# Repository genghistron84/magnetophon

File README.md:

# magnetophon
Small footprint version of Tom Whitwell's Magnetophon module

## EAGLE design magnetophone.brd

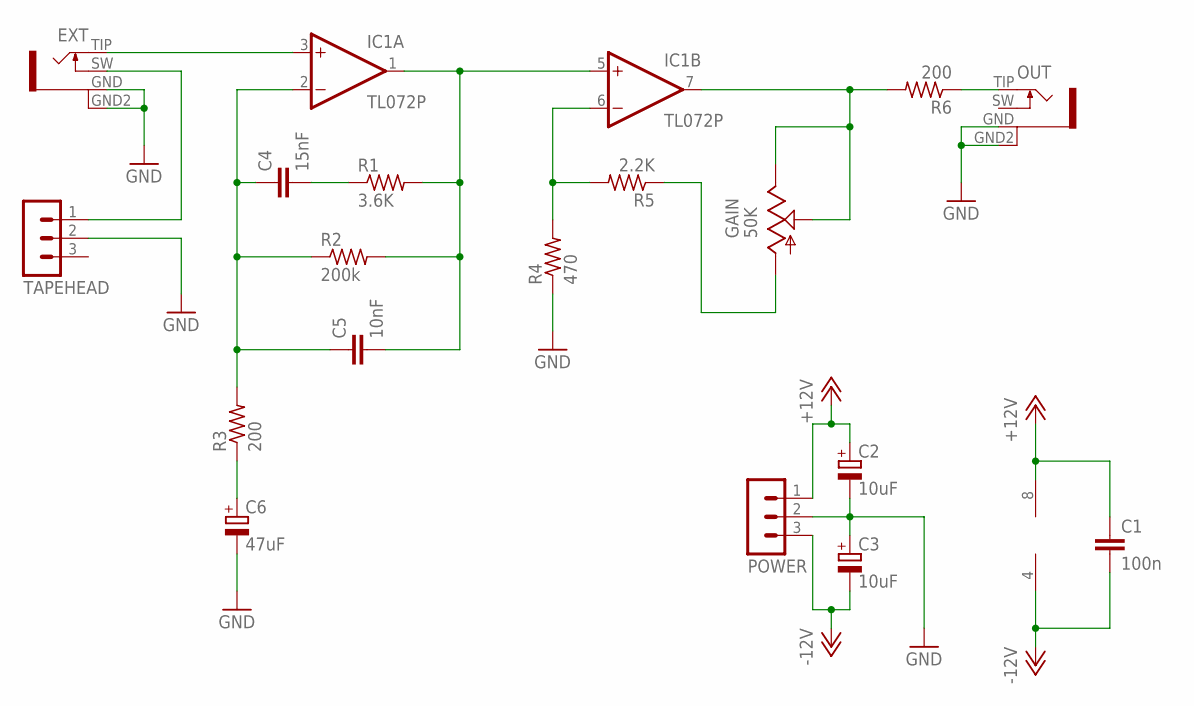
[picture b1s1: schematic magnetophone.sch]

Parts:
C1: 100n; C025-025X050
C2, C3: 10uF; E2,5-6E
C4: 15nF; C025-025X050
C5: 10nF; C025-025X050
C6: 47uF; E2,5-6E
EXT: PJ301BM; PJ301
GAIN: 50K; 9MM_SNAP-IN_POT
IC1: TL072P; DIL08
OUT: PJ301BM; PJ301
POWER: MA03-1
R1: 3.6K; 0207/10
R2: 200k; 0207/10
R3, R6: 200; 0207/10
R4: 470; 0207/10
R5: 2.2K; 0207/10
TAPEHEAD: MA03-1

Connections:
+12V: C1.1, C2.+, IC1.8 (V+), POWER.1
-12V: C1.2, C3.-, IC1.4 (V-), POWER.3
GND: C2.-, C3.+, C6.-, EXT.GND (1), EXT.GND2 (4), OUT.GND (1), OUT.GND2 (4), POWER.2, R4.1, TAPEHEAD.2
unnamed: EXT.SW (3), TAPEHEAD.1
unnamed: C4.1, C5.1, IC1.2 (-IN), R2.1, R3.2
unnamed: C5.2, IC1.1 (OUT), IC1.5 (+IN), R1.2, R2.2
unnamed: C6.+, R3.1
unnamed: EXT.TIP (2), IC1.3 (+IN)
unnamed: C4.2, R1.1
unnamed: IC1.6 (-IN), R4.2, R5.2
unnamed: GAIN.1 (A), R5.1
unnamed: GAIN.2 (S), GAIN.3 (E), IC1.7 (OUT), R6.2
unnamed: OUT.TIP (2), R6.1

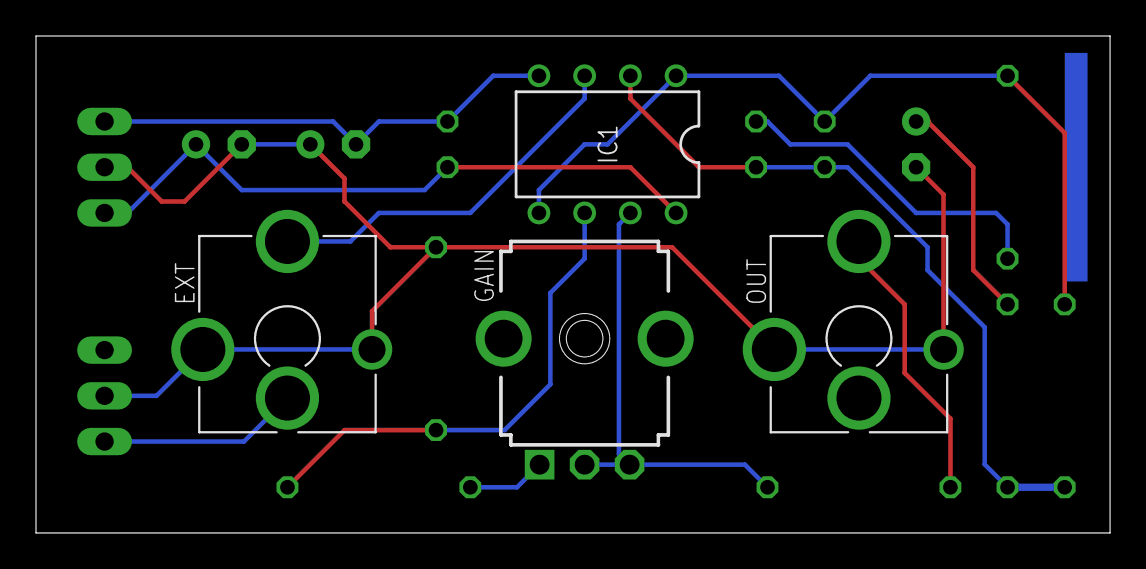
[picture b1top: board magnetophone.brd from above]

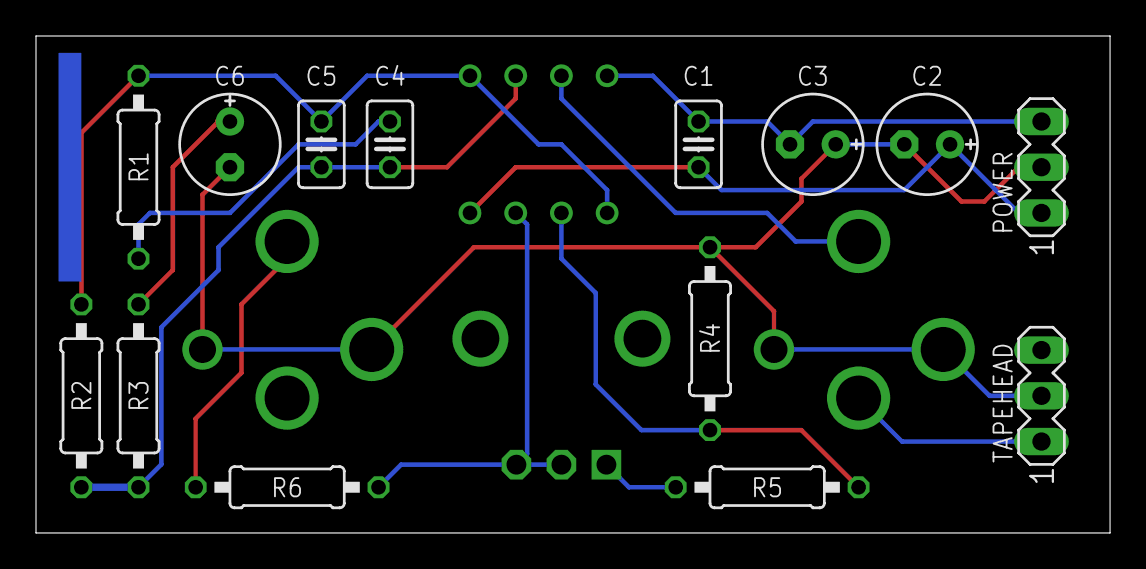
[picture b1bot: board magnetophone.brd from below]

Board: 2 copper layers, 59.7 x 27.6 mm, 18 parts (14 on the bottom side), 13 nets.

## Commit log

2021-11-06 initial Eagle files
2021-11-06 add schematic pdf
2021-11-06 add schematic image
